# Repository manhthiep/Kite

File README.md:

Kite
====

Building a electronics prototyping platform like Arduino/Maple/...

- Kite: mainboard.
- Flut: extension board for Kites.

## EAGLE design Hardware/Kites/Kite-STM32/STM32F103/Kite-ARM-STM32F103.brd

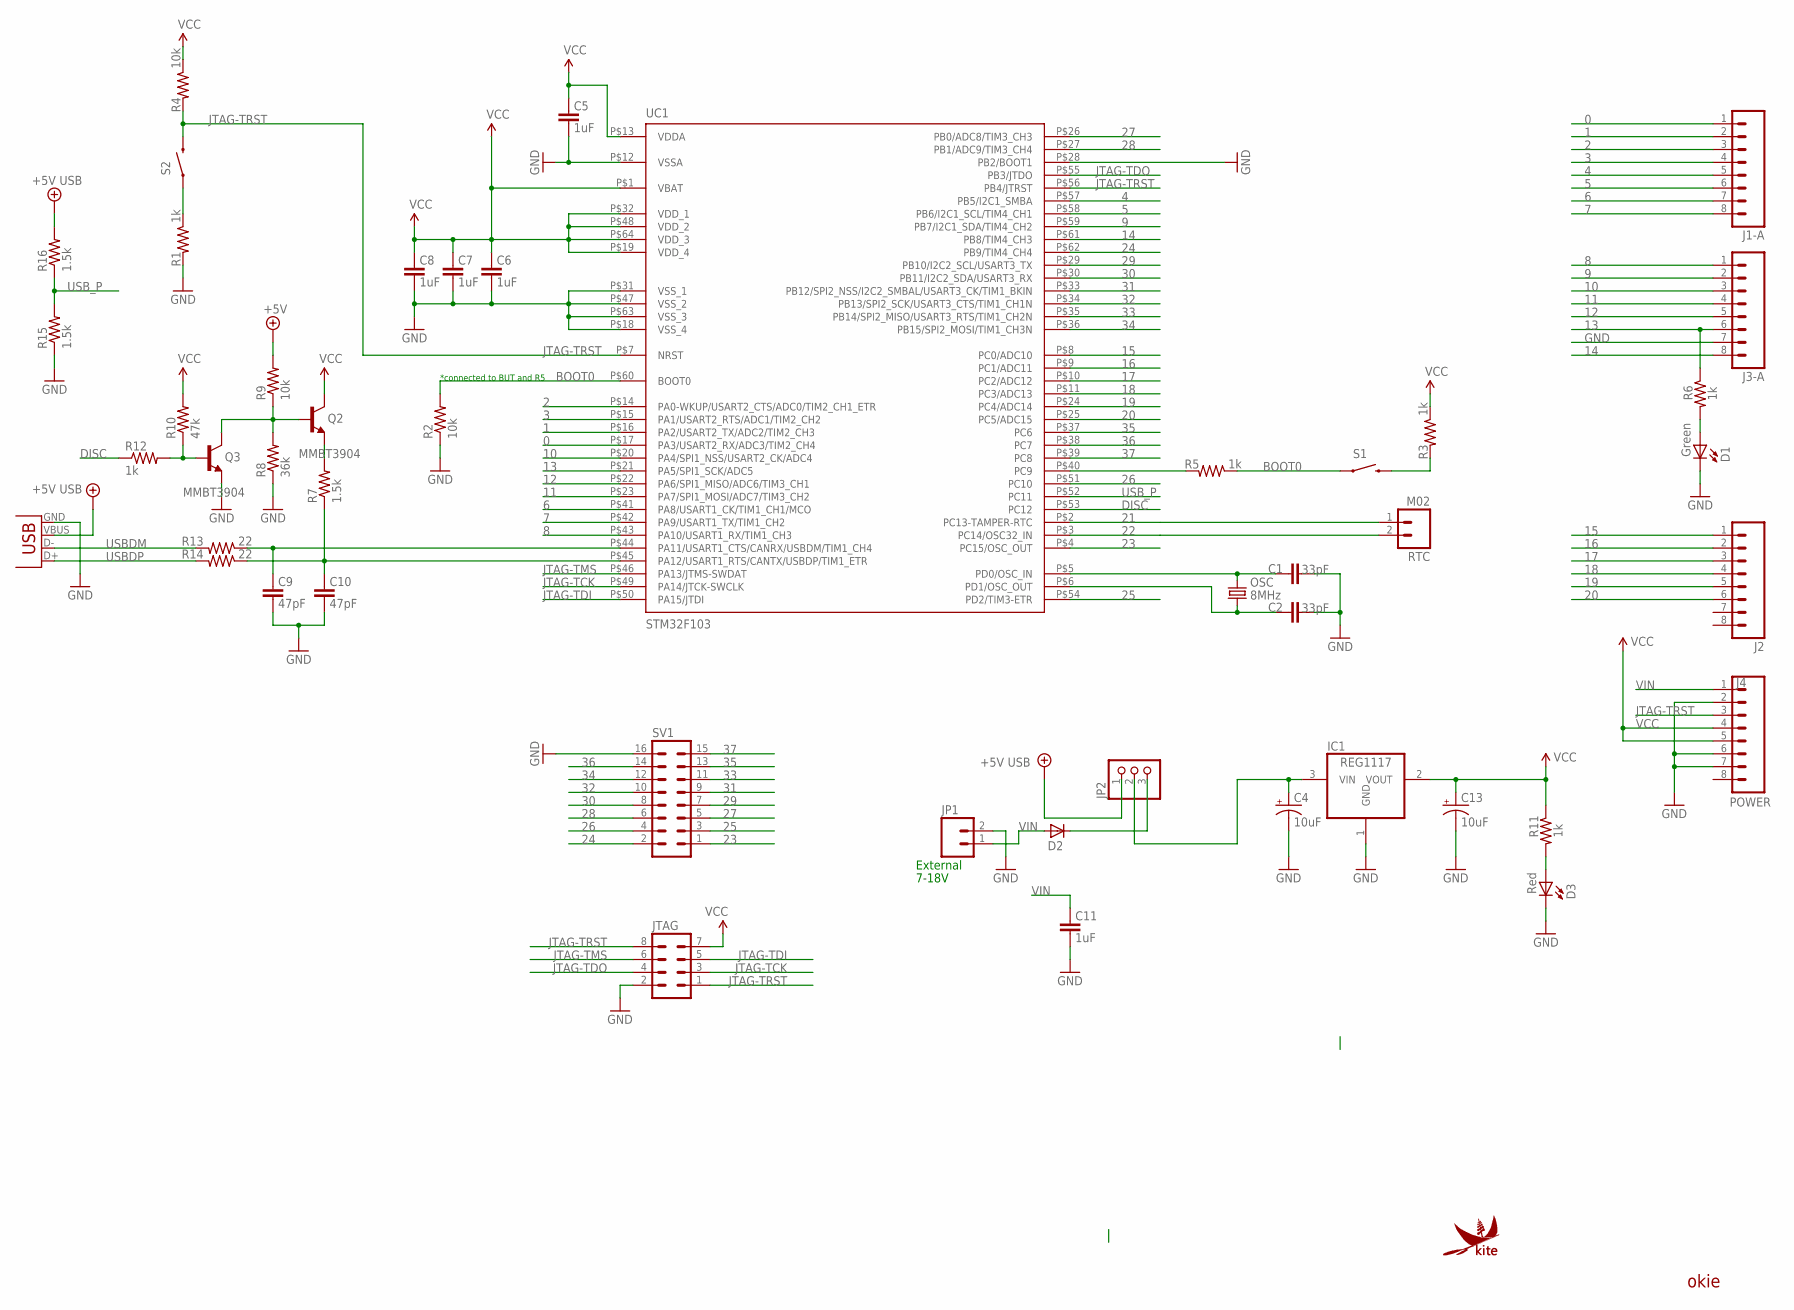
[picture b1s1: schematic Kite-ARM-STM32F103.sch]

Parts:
C1, C2: 33pF; 0603
C4, C13: 10uF; EIA3216
C5, C6, C7, C8, C11: 1uF; 0603
C9, C10: 47pF; 0603
D1: Green; LED-0603
D2: DIODESMA; SMA-DIODE
D3: Red; LED-0603
IC1: REG1117; SOT223
J1-A, J2, J3-A: M081X08; 1X08
J4: POWER; 1X08
JP1: M02POLAR; MOLEX-1X2
JP2: PINHD-1X3; 1X03
JTAG: MA04-2
OSC: 8MHz; CRYSTAL-SMD-5X3
Q2, Q3: MMBT3904; SOT23
R1, R3, R5, R6, R11, R12: 1k; 0603
R2, R4, R9: 10k; 0603
R7, R15, R16: 1.5k; 0603
R8: 36k; 0603
R10: 47k; 0603
R13, R14: 22; 0603
RTC: M02; 1X02
S1, S2: SWITCH-MOMENTARY-2-SMD-1101NE; TACTILE-SWITCH-1101NE
SV1: MA08-2
U$3: KITE-LOGO-STM32-MEDIUM; KITE-STM32-LOGO-MEDIUM
UC1: STM32F103; TQFP-10X10-64
X1: USBSMD; USB-MINIB

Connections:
0: J1-A.1, UC1.P$17 (PA3/USART2_RX/ADC3/TIM2_CH4)
1: J1-A.2, UC1.P$16 (PA2/USART2_TX/ADC2/TIM2_CH3)
2: J1-A.3, UC1.P$14 (PA0-WKUP/USART2_CTS/ADC0/TIM2_CH1_ETR)
3: J1-A.4, UC1.P$15 (PA1/USART2_RTS/ADC1/TIM2_CH2)
4: J1-A.5, UC1.P$57 (PB5/I2C1_SMBA)
5: J1-A.6, UC1.P$58 (PB6/I2C1_SCL/TIM4_CH1)
6: J1-A.7, UC1.P$41 (PA8/USART1_CK/TIM1_CH1/MCO)
7: J1-A.8, UC1.P$42 (PA9/USART1_TX/TIM1_CH2)
8: J3-A.1, UC1.P$43 (PA10/USART1_RX/TIM1_CH3)
9: J3-A.2, UC1.P$59 (PB7/I2C1_SDA/TIM4_CH2)
10: J3-A.3, UC1.P$20 (PA4/SPI1_NSS/USART2_CK/ADC4)
11: J3-A.4, UC1.P$23 (PA7/SPI1_MOSI/ADC7/TIM3_CH2)
12: J3-A.5, UC1.P$22 (PA6/SPI1_MISO/ADC6/TIM3_CH1)
13: J3-A.6, R6.1, UC1.P$21 (PA5/SPI1_SCK/ADC5)
14: J3-A.8, UC1.P$61 (PB8/TIM4_CH3)
15: J2.1, UC1.P$8 (PC0/ADC10)
16: J2.2, UC1.P$9 (PC1/ADC11)
17: J2.3, UC1.P$10 (PC2/ADC12)
18: J2.4, UC1.P$11 (PC3/ADC13)
19: J2.5, UC1.P$24 (PC4/ADC14)
20: J2.6, UC1.P$25 (PC5/ADC15)
21: RTC.1, UC1.P$2 (PC13-TAMPER-RTC)
22: RTC.2, UC1.P$3 (PC14/OSC32_IN)
23: SV1.1, UC1.P$4 (PC15/OSC_OUT)
24: SV1.2, UC1.P$62 (PB9/TIM4_CH4)
25: SV1.3, UC1.P$54 (PD2/TIM3-ETR)
26: SV1.4, UC1.P$51 (PC10)
27: SV1.5, UC1.P$26 (PB0/ADC8/TIM3_CH3)
28: SV1.6, UC1.P$27 (PB1/ADC9/TIM3_CH4)
29: SV1.7, UC1.P$29 (PB10/I2C2_SCL/USART3_TX)
30: SV1.8, UC1.P$30 (PB11/I2C2_SDA/USART3_RX)
31: SV1.9, UC1.P$33 (PB12/SPI2_NSS/I2C2_SMBAL/USART3_CK/TIM1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)
32: SV1.10, UC1.P$34 (PB13/SPI2_SCK/USART3_CTS/TIM1_CH1N)
33: SV1.11, UC1.P$35 (PB14/SPI2_MISO/USART3_RTS/TIM1_CH2N)
34: SV1.12, UC1.P$36 (PB15/SPI2_MOSI/TIM1_CH3N)
35: SV1.13, UC1.P$37 (PC6)
36: SV1.14, UC1.P$38 (PC7)
37: SV1.15, UC1.P$39 (PC8)
+5V: JP2.1, R9.2, R16.2, X1.VBUS
BOOT0: R2.2, R5.1, S1.P$1 (1), UC1.P$60 (BOOT0)
DISC: R12.1, UC1.P$53 (PC12)
GND: C1.1, C2.1, C4.C (-), C5.1, C6.1, C7.1, C8.1, C9.1, C10.1, C11.1, C13.C (-), D1.C, D3.C, IC1.1 (GND), J3-A.7, J4.2, J4.6, J4.7, JP1.2, JTAG.2, Q3.2 (E), R1.2, R2.1, R8.1, R15.1, SV1.16, UC1.P$12 (VSSA), UC1.P$18 (VSS_4), UC1.P$28 (PB2/BOOT1), UC1.P$31 (VSS_1), UC1.P$47 (VSS_2), UC1.P$63 (VSS_3), X1.GND
JTAG-TCK: JTAG.3, UC1.P$49 (PA14/JTCK-SWCLK)
JTAG-TDI: JTAG.5, UC1.P$50 (PA15/JTDI)
JTAG-TDO: JTAG.4, UC1.P$55 (PB3/JTDO)
JTAG-TMS: JTAG.6, UC1.P$46 (PA13/JTMS-SWDAT)
JTAG-TRST: J4.3, JTAG.1, JTAG.8, R4.2, S2.P$2 (2), UC1.P$7 (NRST), UC1.P$56 (PB4/JTRST)
unnamed: D2.C, JP2.3
unnamed: C2.2, OSC.1, UC1.P$6 (PD1/OSC_OUT)
unnamed: C4.A (+), IC1.3 (VIN), JP2.2
unnamed: D3.A, R11.2
unnamed: C1.2, OSC.3 (2), UC1.P$5 (PD0/OSC_IN)
unnamed: D1.A, R6.2
unnamed: Q2.2 (E), R7.2
unnamed: Q2.1 (B), Q3.3 (C), R8.2, R9.1
unnamed: Q3.1 (B), R10.1, R12.2
unnamed: C9.2, R13.1, UC1.P$44 (PA11/USART1_CTS/CANRX/USBDM/TIM1_CH4)
unnamed: C10.2, R7.1, R14.1, UC1.P$45 (PA12/USART1_RTS/CANTX/USBDP/TIM1_ETR)
unnamed: R1.1, S2.P$1 (1)
unnamed: R3.2, S1.P$2 (2)
unnamed: R5.2, UC1.P$40 (PC9)
USBDM: R13.2, X1.D-
USBDP: R14.2, X1.D+
USB_P: R15.2, R16.1, UC1.P$52 (PC11)
VCC: C5.2, C6.2, C7.2, C8.2, C13.A (+), IC1.2 (VOUT), J4.4, J4.5, JTAG.7, Q2.3 (C), R3.1, R4.1, R10.2, R11.1, UC1.P$1 (VBAT), UC1.P$13 (VDDA), UC1.P$19 (VDD_4), UC1.P$32 (VDD_1), UC1.P$48 (VDD_2), UC1.P$64 (VDD_3)
VIN: C11.2, D2.A, J4.1, JP1.1

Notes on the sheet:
External
7-18V
okie
*connected to BUT and R5

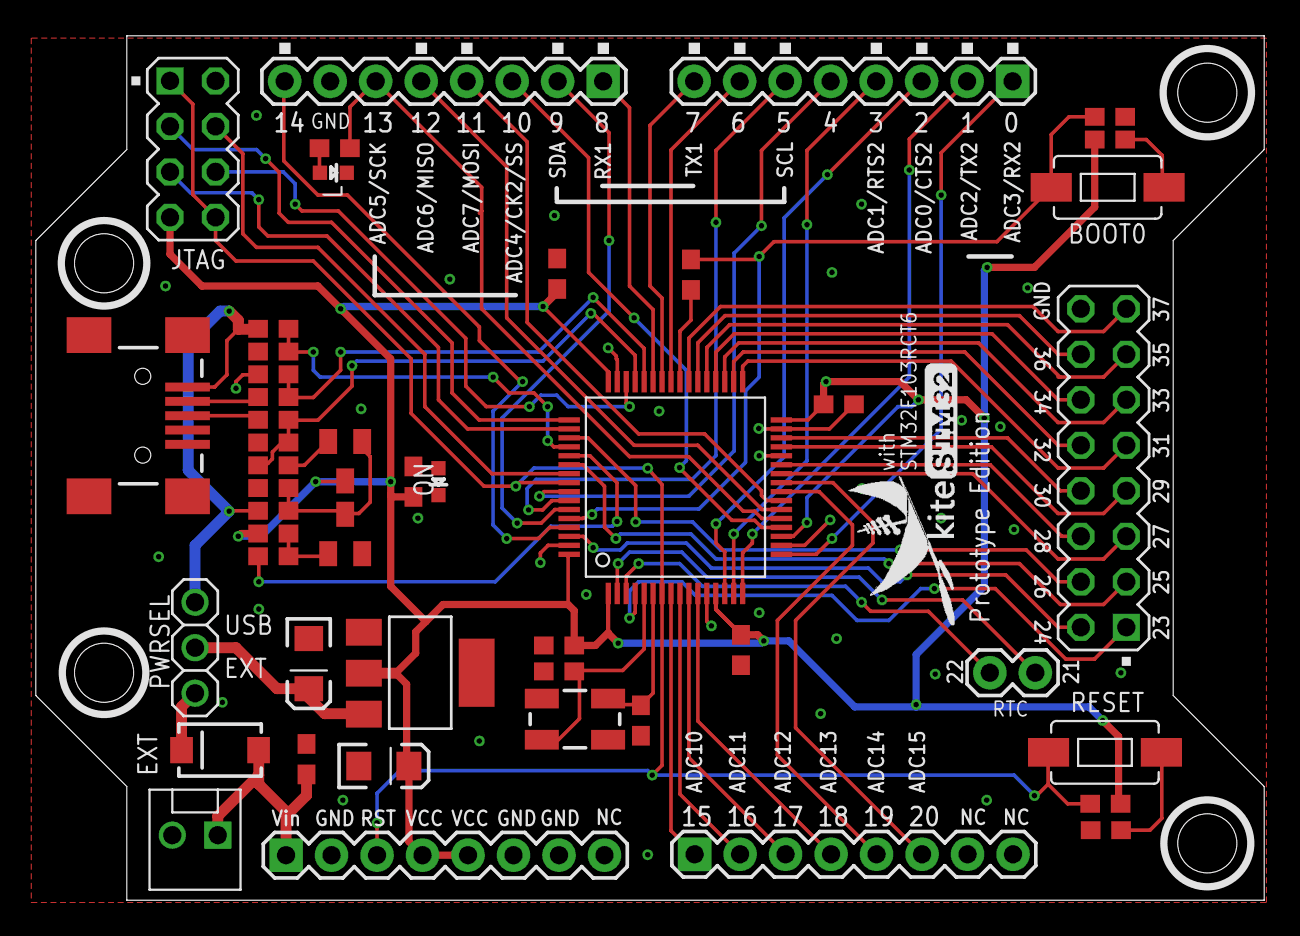
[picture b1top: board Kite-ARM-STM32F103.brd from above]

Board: 2 copper layers, 68.6 x 48.3 mm, 52 parts (0 on the bottom side), 66 nets.

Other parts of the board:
U$1, U$2, U$4, U$10: STAND-OFF

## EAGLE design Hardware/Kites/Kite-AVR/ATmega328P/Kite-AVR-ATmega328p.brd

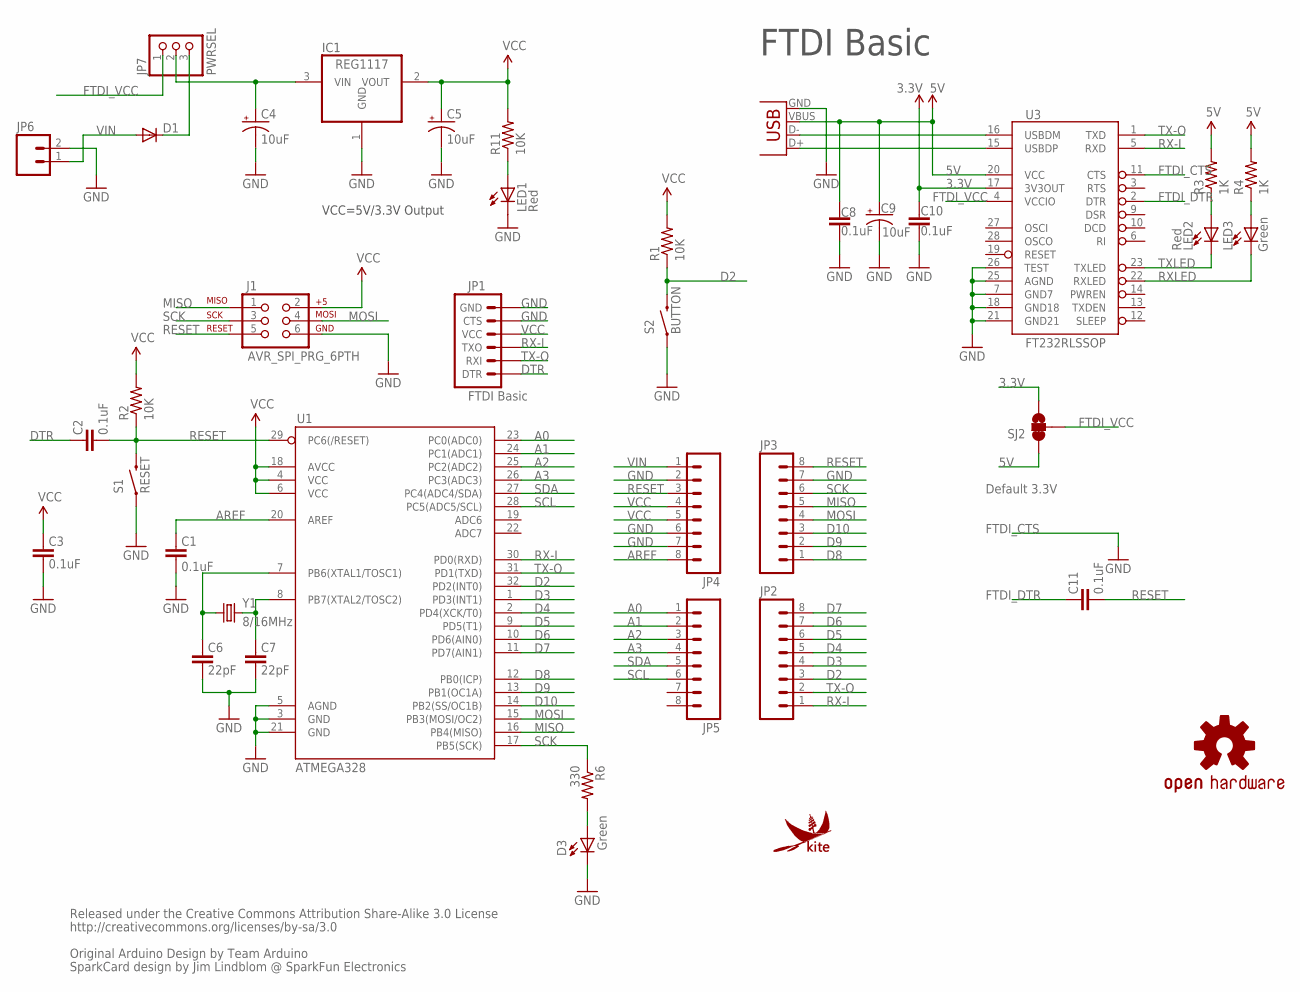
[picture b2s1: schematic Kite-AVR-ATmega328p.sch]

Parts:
C1, C2, C3, C8, C10, C11: 0.1uF; 0603-CAP
C4, C5, C9: 10uF; EIA3216
C6, C7: 22pF; 0603-CAP
D1: DIODESMA; SMA-DIODE
D3: Green; LED-0603
IC1: REG1117; SOT223
J1: AVR_SPI_PRG_6PTH; 2X3
JP1: FTDI Basic; KITE-FTDI
JP2, JP3, JP4, JP5: M081X08; 1X08
JP6: M02POLAR; MOLEX-1X2
JP7: PWRSEL; 1X03
LED1, LED2: Red; LED-0603
LED3: Green; LED-0603
LOGO1: OSHW-LOGOS; OSHW-LOGO-S
R1, R2, R11: 10K; 0603-RES
R3, R4: 1K; 0603-RES
R6: 330; 0603-RES
S1: RESET; TACTILE-SWITCH-1101NE
S2: BUTTON; TACTILE-SWITCH-1101NE
SJ2: SOLDERJUMPER_2WAYS; SJ_3
U1: ATMEGA328; TQFP32-08
U3: FT232RLSSOP; SSOP28DB
U$4: KITE-LOGO-AVR-MEDIUM; KITE-AVR-LOGO-MEDIUM
X2: USB-SMD-NS; USB-MINIB-NOSTOP
Y1: 8/16MHz; CRYSTAL-SMD-5X3

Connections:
3.3V: C10.1, SJ2.3, U3.17 (3V3OUT)
5V: C8.1, C9.A (+), R3.2, R4.2, SJ2.1, U3.20 (VCC), X2.VBUS
A0: JP5.1, U1.23 (PC0(ADC0))
A1: JP5.2, U1.24 (PC1(ADC1))
A2: JP5.3, U1.25 (PC2(ADC2))
A3: JP5.4, U1.26 (PC3(ADC3))
AREF: C1.2, JP4.8, U1.20 (AREF)
D2: JP2.3, R1.1, S2.P$2 (2), U1.32 (PD2(INT0))
D3: JP2.4, U1.1 (PD3(INT1))
D4: JP2.5, U1.2 (PD4(XCK/T0))
D5: JP2.6, U1.9 (PD5(T1))
D6: JP2.7, U1.10 (PD6(AIN0))
D7: JP2.8, U1.11 (PD7(AIN1))
D8: JP3.1, U1.12 (PB0(ICP))
D9: JP3.2, U1.13 (PB1(OC1A))
D10: JP3.3, U1.14 (PB2(SS/OC1B))
DTR: C2.2, JP1.1 (DTR)
FTDI_CTS: U3.11 (CTS)
FTDI_DTR: C11.2, U3.2 (DTR)
FTDI_VCC: JP7.1, SJ2.2, U3.4 (VCCIO)
GND: C1.1, C3.1, C4.C (-), C5.C (-), C6.1, C7.1, C8.2, C9.C (-), C10.2, D3.C, IC1.1 (GND), J1.6, JP1.5 (CTS), JP1.6 (GND), JP3.7, JP4.2, JP4.6, JP4.7, JP6.2, LED1.C, S1.P$1 (1), S2.P$1 (1), U1.3 (GND), U1.5 (AGND), U1.21 (GND), U3.7 (GND7), U3.18 (GND18), U3.21 (GND21), U3.25 (AGND), U3.26 (TEST), X2.GND
MISO: J1.1, JP3.5, U1.16 (PB4(MISO))
MOSI: J1.4, JP3.4, U1.15 (PB3(MOSI/OC2))
unnamed: C7.2, U1.8 (PB7(XTAL2/TOSC2)), Y1.3 (2)
unnamed: C6.2, U1.7 (PB6(XTAL1/TOSC1)), Y1.1
unnamed: LED2.A, R3.1
unnamed: C4.A (+), IC1.3 (VIN), JP7.2
unnamed: LED3.A, R4.1
unnamed: D3.A, R6.2
unnamed: D1.C, JP7.3
unnamed: LED1.A, R11.1
RESET: C2.1, C11.1, J1.5, JP3.8, JP4.3, R2.1, S1.P$2 (2), U1.29 (PC6(/RESET))
RX-I: JP1.3 (TXO), JP2.1, U1.30 (PD0(RXD)), U3.5 (RXD)
RXLED: LED3.C, U3.22 (RXLED)
SCK: J1.3, JP3.6, R6.1, U1.17 (PB5(SCK))
SCL: JP5.6, U1.28 (PC5(ADC5/SCL))
SDA: JP5.5, U1.27 (PC4(ADC4/SDA))
TX-O: JP1.2 (RXI), JP2.2, U1.31 (PD1(TXD)), U3.1 (TXD)
TXLED: LED2.C, U3.23 (TXLED)
USB_D+: U3.15 (USBDP), X2.D+
USB_D-: U3.16 (USBDM), X2.D-
VCC: C3.2, C5.A (+), IC1.2 (VOUT), J1.2, JP1.4 (VCC), JP4.4, JP4.5, R1.2, R2.2, R11.2, U1.4 (VCC), U1.6 (VCC), U1.18 (AVCC)
VIN: D1.A, JP4.1, JP6.1

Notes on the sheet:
Released under the Creative Commons Attribution Share-Alike 3.0 License
http://creativecommons.org/licenses/by-sa/3.0
Original Arduino Design by Team Arduino
SparkCard design by Jim Lindblom @ SparkFun Electronics
VCC=5V/3.3V Output
Default 3.3V
FTDI Basic

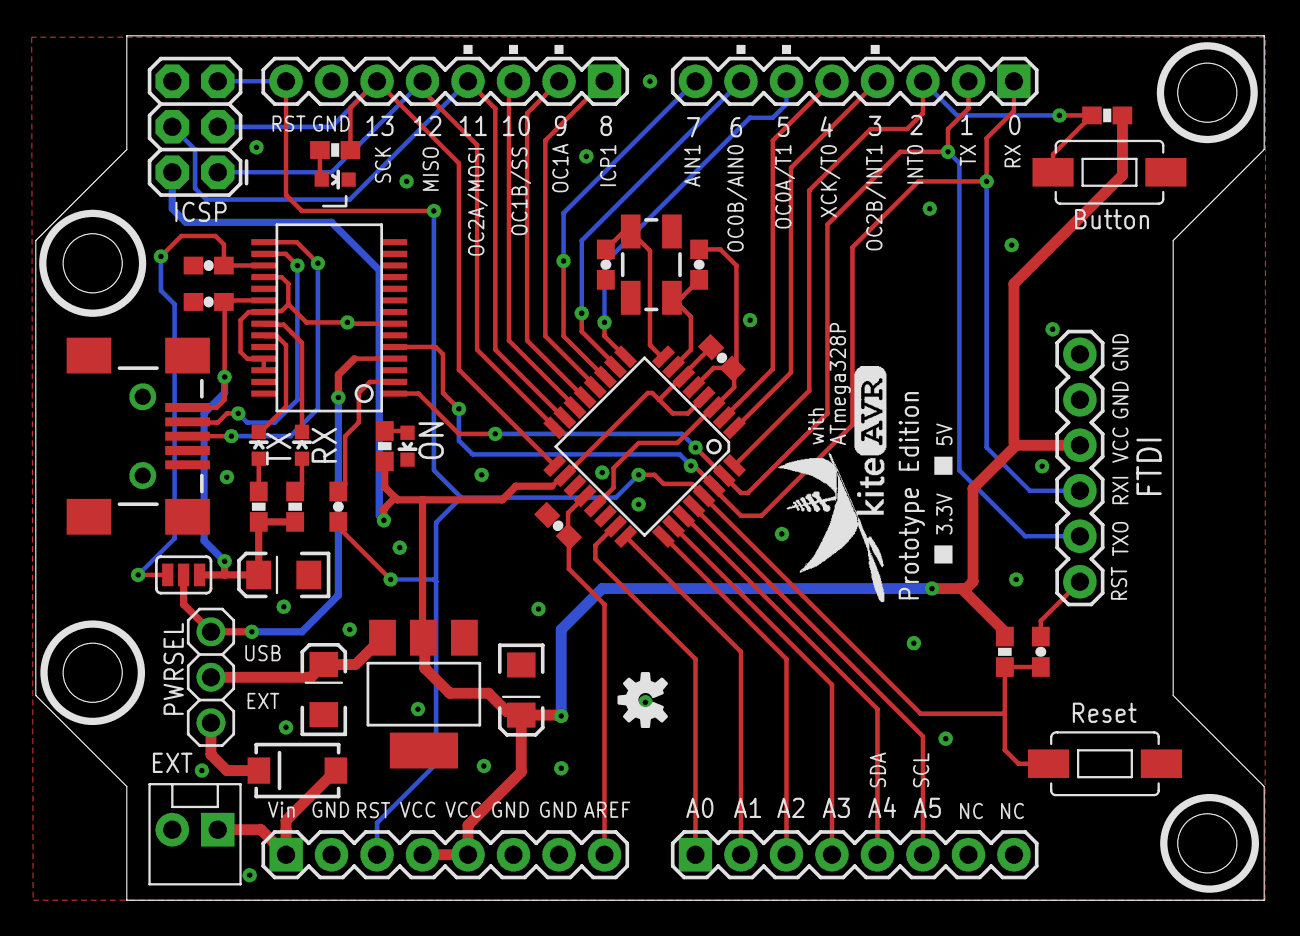
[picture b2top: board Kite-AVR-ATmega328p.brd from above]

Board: 2 copper layers, 68.6 x 48.3 mm, 44 parts (0 on the bottom side), 42 nets.

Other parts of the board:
U$2, U$3, U$5, U$6: STAND-OFF

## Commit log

2013-12-04 Initial imports

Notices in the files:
parts and their libraries:
SparkFun-Connectors: Licensing: CC v3.0 Share-Alike You are welcome to use this library for commercial purposes.
